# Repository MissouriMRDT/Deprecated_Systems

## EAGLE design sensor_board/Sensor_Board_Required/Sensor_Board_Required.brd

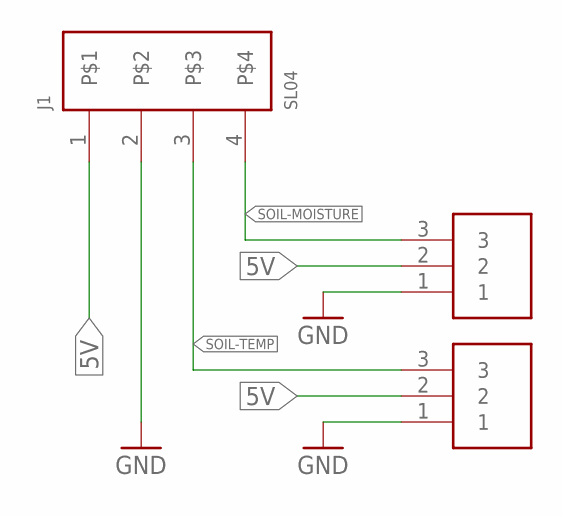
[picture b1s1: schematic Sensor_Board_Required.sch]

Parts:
J1: SL04; MOLEX_SL_04_TH
J2, J3: SL03THROUGH_HOLE; MOLEX_SL_03_TH

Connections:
5V: J1.1, J2.2, J3.2
GND: J1.2, J2.1, J3.1
SOIL-MOISTURE: J1.4, J2.3
SOIL-TEMP: J1.3, J3.3

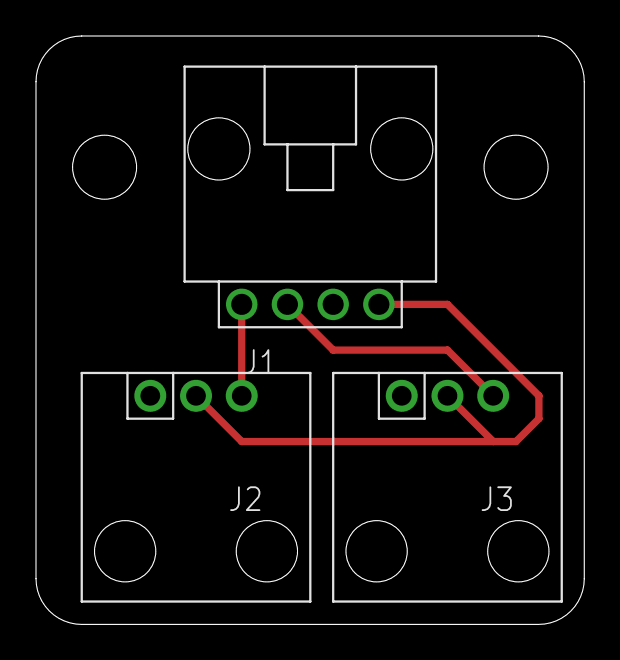
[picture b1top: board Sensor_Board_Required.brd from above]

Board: 2 copper layers, 30.5 x 32.7 mm, 5 parts (0 on the bottom side), 4 nets.

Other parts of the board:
U$1, U$2: #6_SCREW

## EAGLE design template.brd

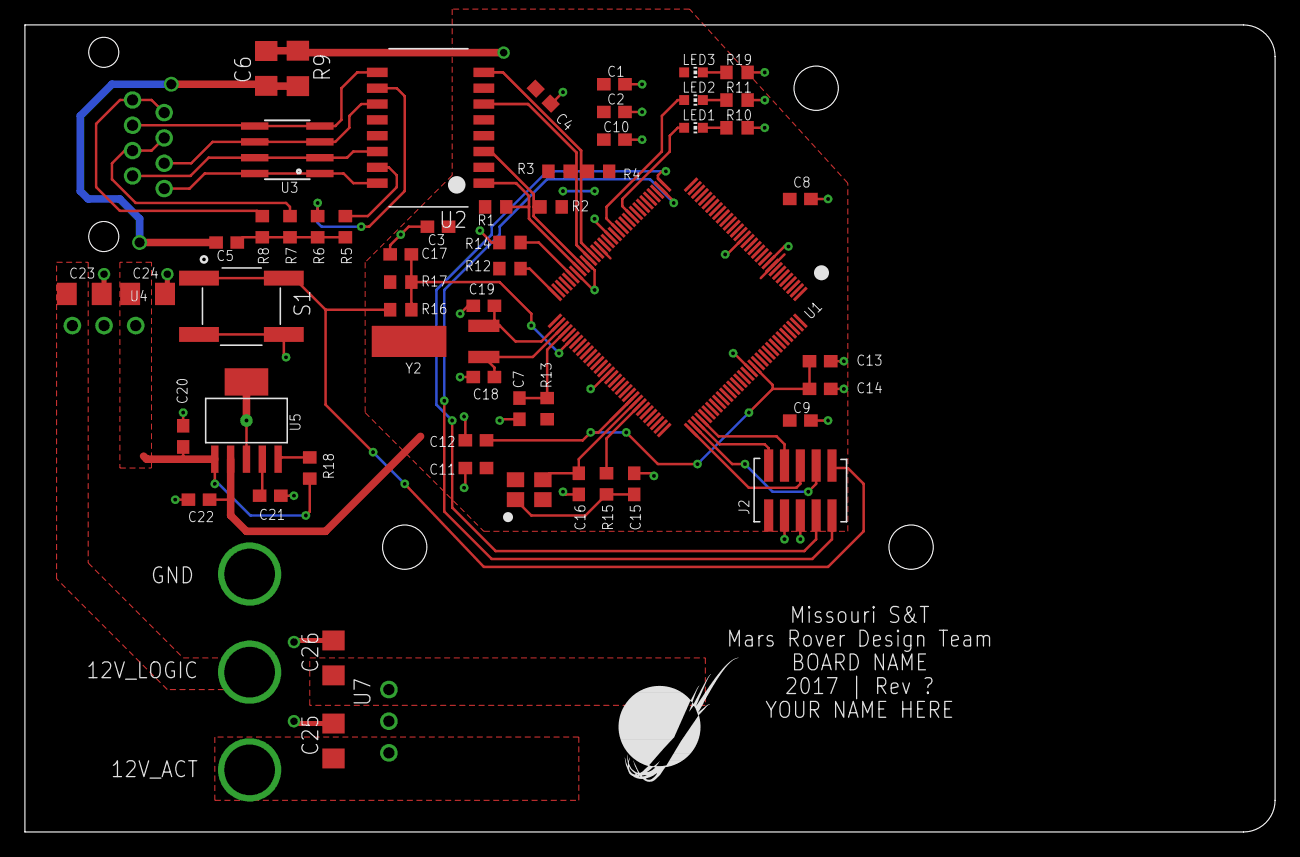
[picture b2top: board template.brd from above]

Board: 2 copper layers, 100.3 x 64.8 mm, 65 parts (0 on the bottom side), 44 nets.

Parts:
C1, C2, C3, C4, C7, C8, C9, C10, C11, C12, C17, C20, C21: 0.1uF; C0603
C5: 1000pF; C0603
C6: 4700pF; C1206
C13: 1.0uF; C0603
C14, C22: 2.2uF; C0603
C15, C16, C18, C19: 12pF; C0603
C23, C24, C25, C26: 10uF; C1206
J1: RJ45KEYSTONE-942; KEYSTONE-942
J2: JTAG_ARM_10PIN; CON_2X5_50MIL
J3: APP_2POS_CONFIG12V_HORIZ; APP45_12V_HORIZ_CONFIG
J8: APPPP45_PCB_HORIZ_RIGHT; APP45_PCB_HORIZ_RIGHT
LED1, LED2: GREEN; CHIP-LED0603
LED3: ORANGE; CHIP-LED0603
R1, R3, R4: 49.9; R0603
R2: 49.4; R0603
R5, R6, R7, R8: 75; R0603
R9: 1M; R1206
R10, R11, R19: 330; R0603
R12: 1M; R0603
R13: 51; R0603
R14: 4.87k 1%; R0603
R15: 2k; R0603
R16: 100; R0603
R17: 10k; R0603
R18: 100k; R0603
S1: SWITCH_TACTILE; SWITCH_6MM_6MM_TE_CON_SMD
U1: TM4C1294NCPDT; TQFP-128
U2: HX1198FNL
U3: SLVU2.8-4; SOIC8
U4, U7: OKI-78SR-5/1.5-W36HC; OKI-78SR_HORIZ
U5: TPS73733DCQ; SOT-223-6
U$1: MRDT_LOGO
U$2, U$3, U$4: MOUNTING_HOLE#6; #6_SCREW
Y1: NX3225GA; NDK3.2X2.5
Y2: CRYATL_32K_SMD; CRYSTAL_32K_SMD

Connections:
!RESET: J2.P10, R16.2, S1.P$3, S1.P$4
+3V3: C1.1, C2.1, C3.1, C4.1, C8.1, C9.1, C10.1, C11.1, C22.1, J2.P1, LED3.A, R1.1, R2.1, R3.1, R4.1, R12.2, R13.2, R17.1, U1.P$7, U1.P$8, U1.P$9, U1.P$16, U1.P$26, U1.P$28, U1.P$39, U1.P$47, U1.P$51, U1.P$52, U1.P$69, U1.P$79, U1.P$90, U1.P$101, U1.P$113, U1.P$122, U2.P$2, U2.P$7, U5.2
+5V_ACT: C26.1, U7.3
+5V_LOGIC: C20.1, C24.1, R18.1, U4.3, U5.1
+12V_ACT: C25.1, J8.P$1, U7.1
+12V_LOGIC: C23.1, J3.12V, U4.1
EN0LED0: LED1.A, U1.P$42
EN0LED1: LED2.A, U1.P$46
EN0RXI_N: R4.2, U1.P$53, U2.P$8
EN0RXI_P: R3.2, U1.P$54, U2.P$6
EN0TXO_N: R2.2, U1.P$56, U2.P$3
EN0TXO_P: R1.2, U1.P$57, U2.P$1
GND: C1.2, C2.2, C3.2, C4.2, C6.2, C7.2, C8.2, C9.2, C10.2, C11.2, C12.2, C13.2, C14.2, C15.2, C16.2, C17.2, C18.2, C19.2, C20.2, C21.2, C22.2, C23.2, C24.2, C25.2, C26.2, J2.P3, J2.P5, J3.GND, R9.1, R10.2, R11.2, R14.1, R19.2, S1.P$1, S1.P$2, U1.P$10, U1.P$17, U1.P$48, U1.P$55, U1.P$58, U1.P$80, U1.P$114, U4.2, U5.3, U5.6, U7.2
N_$1: R5.2, U2.P$15
N_$3: R6.2, U2.P$10
N_$4: J1.P$7, U2.P$14, U3.2, U3.7
N_$5: J1.P$6, U2.P$11, U3.3, U3.6
N_$6: J1.P$8, U2.P$16, U3.1, U3.8
N_$7: J1.P$3, U2.P$9, U3.4, U3.5
N_$8: LED2.C, R11.1
N_$9: LED1.C, R10.1
N_$10: C7.1, R13.1, U1.P$68
N_$11: J1.P$4, J1.P$5, R7.2
N_$12: R12.1, U1.P$64
N_$13: J1.P$1, J1.P$2, R8.2
N_$14: C5.1, R5.1, R6.1, R7.1, R8.1
N_$15: C5.2, C6.1, R9.2
N_$16: C12.1, C13.1, C14.1, U1.P$87, U1.P$115
N_$17: R15.2, U1.P$89
N_$18: C16.1, U1.P$88, Y1.P$3
N_$19: R14.2, U1.P$59
N_$20: C17.1, R16.1, R17.2, U1.P$70
N_$21: C15.1, R15.1, Y1.P$1
N_$22: C18.1, U1.P$67, Y2.P$2
N_$23: C19.1, U1.P$66, Y2.P$1
N_$25: R18.2, U5.5
N_$26: LED3.C, R19.1
N_$27: C21.1, U5.4
RX: J2.P7, U1.P$33
TARGET_TCK/SWCLK: J2.P4, U1.P$100
TARGET_TDI: J2.P8, U1.P$98
TARGET_TDO/SWO: J2.P6, U1.P$97
TARGET_TMS/SWDIO: J2.P2, U1.P$99
TX: J2.P9, U1.P$34
